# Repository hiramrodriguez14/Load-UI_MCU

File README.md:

# Horizontal Axis Wind Turbine Electronic Control Unit (ECU)

## Load Control & User Interface PCB

Printed Circuit Board (PCB) design for the **Load Control & User Interface (Load & UI) MCU** of the **Horizontal Axis Wind Turbine Electronic Control Unit (ECU)**.

This repository contains the complete KiCad hardware design, manufacturing files, and production documentation for the embedded controller responsible for battery charging, power management, user interaction, and system monitoring.

---

# Documentation & Demo

| Resource | Link |
| ------------------------ | ------------------------------- |
| 🎥 Project Demonstration | https://www.youtube.com/watch?v=vS5Ok38P1Jk |
| 📄 Final Project Report | https://drive.google.com/file/d/1cckKhvj7mvzCEbm3IqWp0KvrUp9g6mgg/view?usp=sharing |
| 📚 Technical Appendix | https://drive.google.com/file/d/1xu7MtcffDlpna8_BUkwEc_BfjpQJpUep/view?usp=sharing |

---

# Overview

The Load Control & User Interface PCB serves as the primary electrical control board of the Horizontal Axis Wind Turbine Electronic Control Unit (ECU).

Designed using **KiCad**, this board integrates sensing, power management, user interaction, communication, and data logging into a single embedded platform. It operates alongside the Turbine MCU PCB to provide complete supervision of the wind turbine system.

The PCB was designed with debugging, manufacturability, and future expansion in mind, incorporating dedicated test points, modular circuitry, and production-ready manufacturing files.

---

# Engineering Highlights

- Custom 2-layer PCB
- Designed in KiCad
- Texas Instruments MSPM0G3519
- Dual INA229 Power Monitors
- SEPIC Converter Control
- Battery Management System (BMS)
- LCD User Interface
- Push Button Interface
- Status LEDs
- UART Communication
- microSD Card Interface
- Relay Driver
- Barrel Jack Power Input
- Production-ready Gerber files
- Pick-and-Place (CPL) files
- Manufacturing BOM

---

# Hardware Features

The PCB integrates the following subsystems:

### Power Management

- Battery charging controller
- SEPIC converter interface
- Power monitoring
- Relay control
- Load protection

### User Interface

- 20×4 LCD connector
- Navigation buttons
- Record button
- Start / Stop controls
- Status LEDs

### Communication

- UART interface to Turbine MCU
- Programming interface
- Debug connectors

### Data Logging

- microSD card socket
- Real-Time Clock (RTC)

---

# Hardware Architecture

The Load Control & UI PCB serves as the electrical management hub of the complete ECU.

Primary functions include:

- Battery charging
- Converter control
- Power measurement
- User interaction
- Data logging
- Load protection
- Communication with the Turbine MCU

<p align="center">
<b>Figure 1.</b> Load & UI MCU Architecture
</p>

---

# PCB Design

The board was designed using KiCad following standard PCB design practices for embedded systems.

Design considerations include:

- Component placement optimization
- Short signal routing
- Power integrity
- Ground plane utilization
- Test point accessibility
- Manufacturing compatibility

## Top Layer

<p align="center">
<b>Figure 2.</b> Top Layer PCB Layout
</p>

---

## Bottom Layer

<p align="center">
<b>Figure 3.</b> Bottom Layer PCB Layout
</p>

---

## Combined Layer View

<p align="center">
<b>Figure 4.</b> Combined PCB Layers
</p>

---

## 3D PCB View

<p align="center">
<b>Figure 5.</b> 3D PCB Rendering
</p>

---

# Manufacturing Files

This repository includes all files required for PCB fabrication and assembly.

Included manufacturing assets:

- Gerber files
- Drill files
- Pick-and-Place (CPL)
- Bill of Materials (BOM)
- Complete schematic
- PCB layout

---

# Development Tools

## PCB Design

- KiCad

## Target MCU

- Texas Instruments MSPM0G3519

---

# Repository Structure

```text
HAWT-LoadUI-PCB
│
├── gerbers/                    Manufacturing Gerber files
├── images/                     Documentation images
├── mylib/                      Custom KiCad component library
├── Load-UI_MCU.kicad_pcb       PCB layout
├── Load-UI_MCU.kicad_sch       Main schematic
├── Load-UI_MCU.kicad_pro       KiCad project
├── Load-UI_MCU-final.csv       Manufacturing BOM
├── Load-UI_MCU-all-pos.csv     Pick-and-Place (CPL)
├── load.kicad_sch              Power subsystem schematic
├── ui.kicad_sch                User Interface schematic
├── README.md                   Repository documentation
└── LICENSE                     Project license
```

---

# Related Repositories

| Repository | Description |
| ------------------------ | ----------------------------------------------- |
| HAWT-TurbineMCU-Firmware | Turbine control firmware |
| HAWT-Load_Control_and_UI | Load Control & UI firmware |
| Turbine_MCU              | Turbine MCU PCB |

---

# Authors

- Hiram R. Rodríguez Hernández
- José M. Burgos Guntín
- Sergio A. Meléndez Padilla
- Sergio A. Da Silva López

Department of Electrical & Computer Engineering

University of Puerto Rico – Mayagüez

---

# License

This project was developed for educational and research purposes as part of the Embedded Systems Design course at the University of Puerto Rico – Mayagüez.

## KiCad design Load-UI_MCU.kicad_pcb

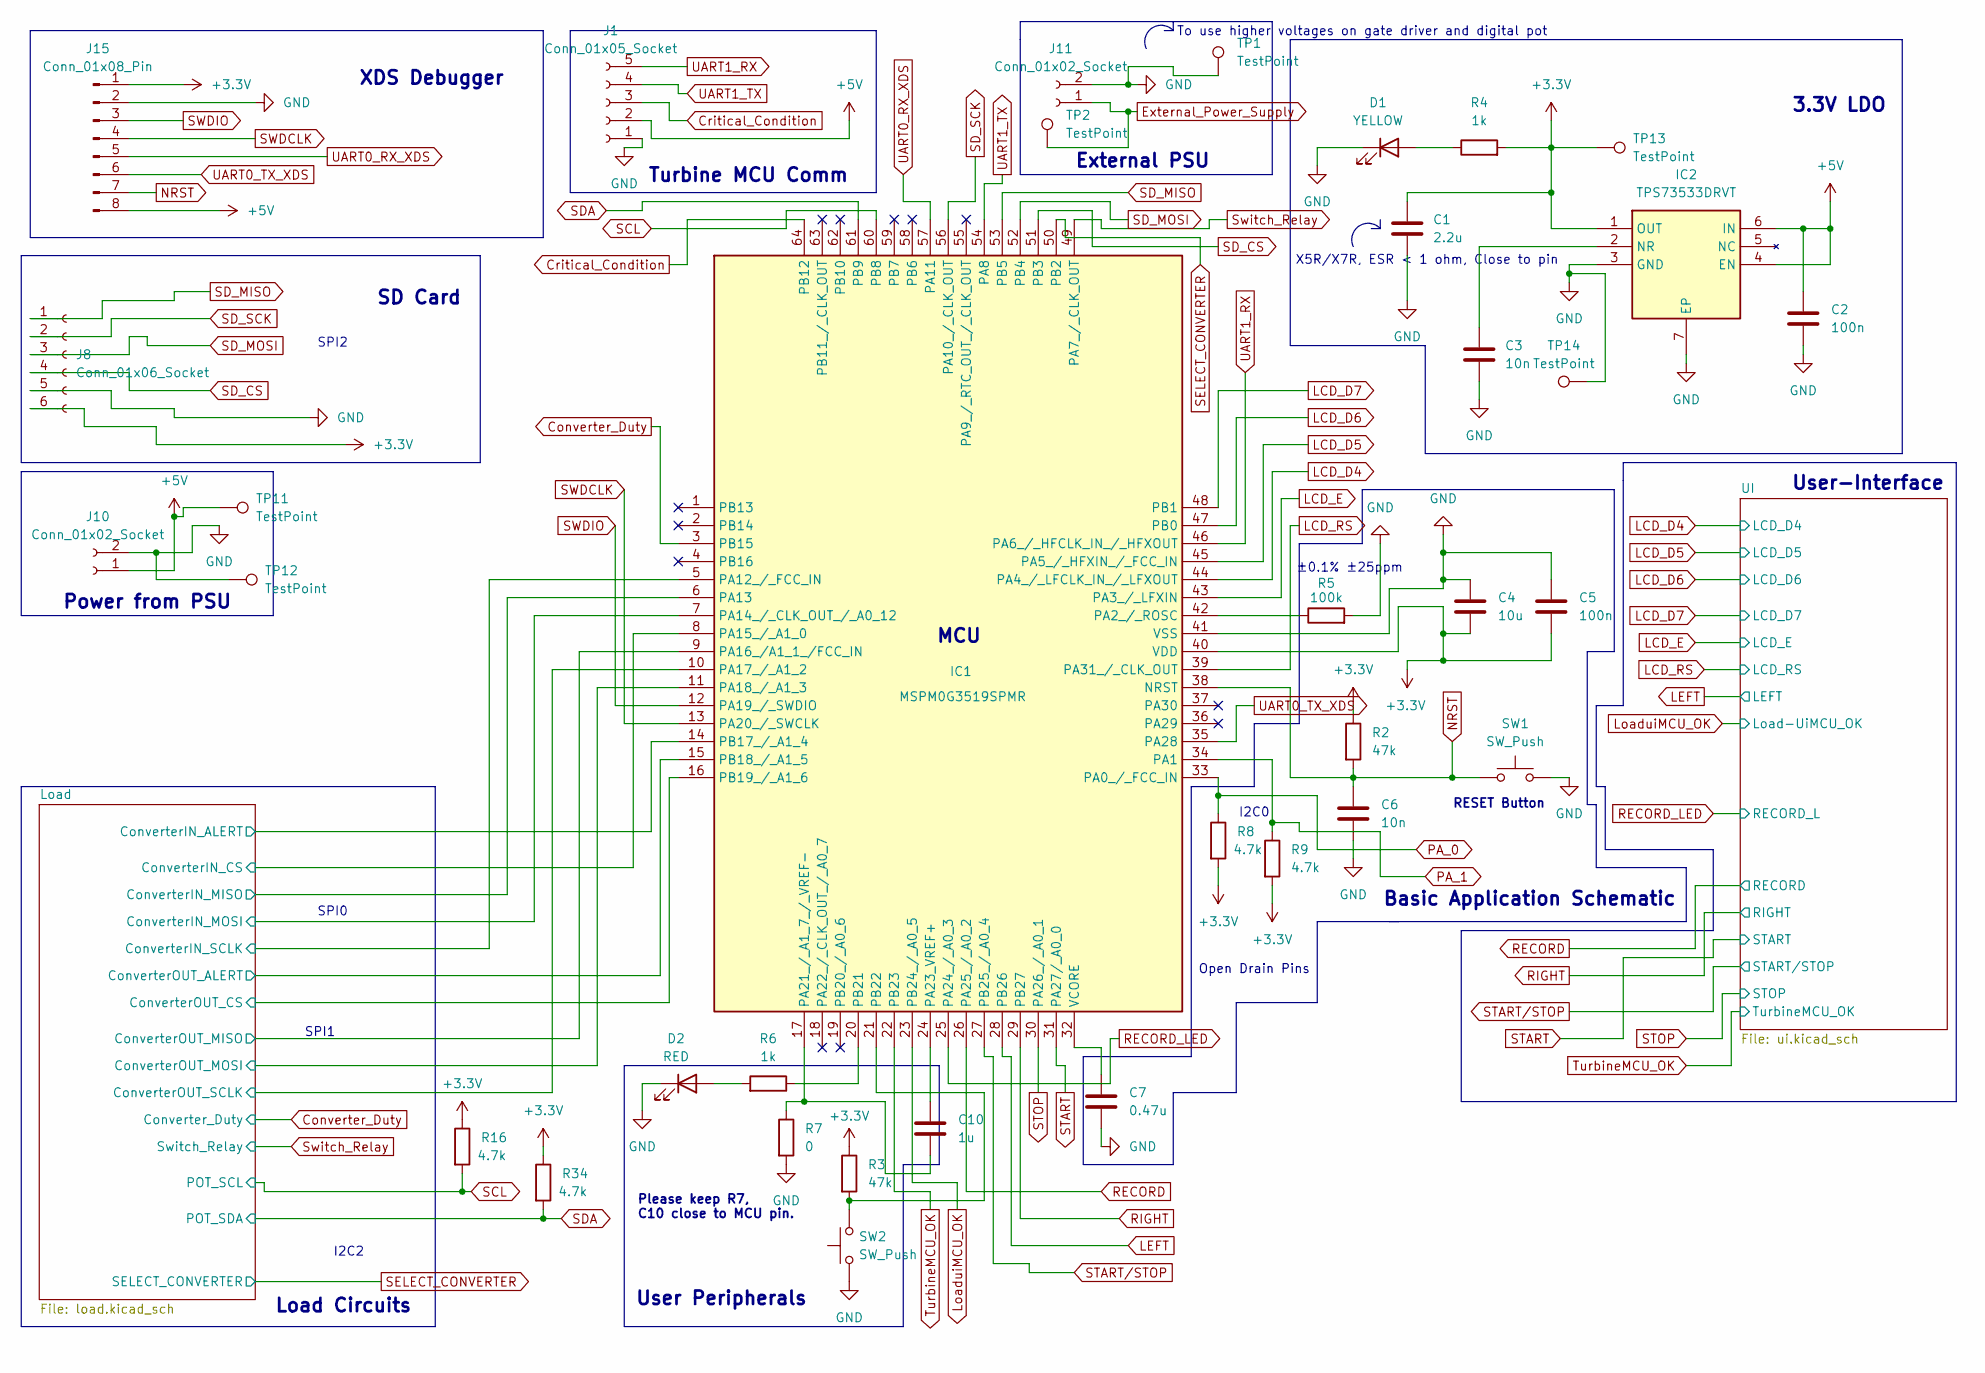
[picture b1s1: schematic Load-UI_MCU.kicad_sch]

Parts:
C1: 2.2u; C_1206_3216Metric_Pad1.33x1.80mm_HandSolder
C2, C5: 100n; C_0805_2012Metric_Pad1.18x1.45mm_HandSolder
C3: 10n; C_0402_1005Metric_Pad0.74x0.62mm_HandSolder
C4: 10u; C_1206_3216Metric_Pad1.33x1.80mm_HandSolder
C6: 10n; C_1206_3216Metric_Pad1.33x1.80mm_HandSolder
C7: 0.47u; C_0805_2012Metric_Pad1.18x1.45mm_HandSolder
C10: 1u; C_0402_1005Metric_Pad0.74x0.62mm_HandSolder
D1: YELLOW; LED_0805_2012Metric_Pad1.15x1.40mm_HandSolder
D2: RED; LED_0603_1608Metric_Pad1.05x0.95mm_HandSolder
IC1: MSPM0G3519SPMR; QFP50P1200X1200X160-64N; Mouser Part Number 595-MSPM0G3507SPMR
IC2: TPS73533DRVT; SON65P200X200X80-7N; Mouser Part Number 595-TPS73533DRVT
J1: Conn_01x05_Socket; JST_XH_B5B-XH-A_1x05_P2.50mm_Vertical
J8: Conn_01x06_Socket; JST_XH_B6B-XH-A_1x06_P2.50mm_Vertical
J10, J11: Conn_01x02_Socket; TerminalBlock_Xinya_XY308-2.54-2P_1x02_P2.54mm_Horizontal
J15: Conn_01x08_Pin; PinHeader_1x08_P2.54mm_Vertical
R2, R3: 47k; R_0805_2012Metric_Pad1.20x1.40mm_HandSolder
R4: 1k; R_0805_2012Metric_Pad1.20x1.40mm_HandSolder
R5: 100k; R_0603_1608Metric_Pad0.98x0.95mm_HandSolder
R6: 1k; R_1206_3216Metric_Pad1.30x1.75mm_HandSolder
R7: 0; R_0402_1005Metric_Pad0.72x0.64mm_HandSolder
R8, R9, R16, R34: 4.7k; R_0805_2012Metric_Pad1.20x1.40mm_HandSolder
SW1, SW2: SW_Push; SW_PUSH_6mm
TP1, TP2, TP11, TP12, TP13, TP14: TestPoint; TestPoint_Pad_D1.0mm

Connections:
+3.3V: C1.1, C4.2, C5.2, IC1.40 (VDD), IC2.1 (OUT), J8.6, J15.1, R2.1, R3.1, R4.2, R8.2, R9.2, R16.1, R34.1, TP13.1; also elsewhere on the board
+5V: C2.1, IC2.4 (EN), IC2.6 (IN), J1.2, J10.1, J15.8, TP11.1; also elsewhere on the board
/Load/ConverterIN_ALERT: IC1.14 (PB17_/_A1_4); also elsewhere on the board
/Load/ConverterIN_CS: IC1.8 (PA15_/_A1_0); also elsewhere on the board
/Load/ConverterIN_MISO: IC1.6 (PA13); also elsewhere on the board
/Load/ConverterIN_MOSI: IC1.7 (PA14_/_CLK_OUT_/_A0_12); also elsewhere on the board
/Load/ConverterIN_SCLK: IC1.5 (PA12_/_FCC_IN); also elsewhere on the board
/Load/ConverterOUT_ALERT: IC1.15 (PB18_/_A1_5); also elsewhere on the board
/Load/ConverterOUT_CS: IC1.16 (PB19_/_A1_6); also elsewhere on the board
/Load/ConverterOUT_MISO: IC1.9 (PA16_/A1_1_/FCC_IN); also elsewhere on the board
/Load/ConverterOUT_MOSI: IC1.11 (PA18_/_A1_3); also elsewhere on the board
/Load/ConverterOUT_SCLK: IC1.10 (PA17_/_A1_2); also elsewhere on the board
Converter_Duty: IC1.3 (PB15); also elsewhere on the board
Critical_Condition: IC1.64 (PB12), J1.3
External_Power_Supply: J11.1, TP2.1; also elsewhere on the board
GND: C1.2, C2.2, C3.2, C4.1, C5.1, C6.2, C7.2, D1.1 (K), D2.1 (K), IC1.41 (VSS), IC2.3 (GND), IC2.7 (EP), J1.1, J8.5, J10.2, J11.2, J15.2, R5.2, R7.2, SW1.2, SW2.1, TP1.1, TP12.1, TP14.1; also elsewhere on the board
LCD_D4: IC1.44 (PA4_/_LFCLK_IN_/_LFXOUT); also elsewhere on the board
LCD_D5: IC1.45 (PA5_/_HFXIN_/_FCC_IN); also elsewhere on the board
LCD_D6: IC1.47 (PB0); also elsewhere on the board
LCD_D7: IC1.48 (PB1); also elsewhere on the board
LCD_E: IC1.43 (PA3_/_LFXIN); also elsewhere on the board
LCD_RS: IC1.39 (PA31_/_CLK_OUT); also elsewhere on the board
LEFT: IC1.28 (PB26); also elsewhere on the board
LoaduiMCU_OK: IC1.23 (PB24_/_A0_5); also elsewhere on the board
NRST: C6.1, IC1.38 (NRST), J15.7, R2.2, SW1.1; also elsewhere on the board
unnamed: D1.2 (A), R4.1
unnamed: D2.2 (A), R6.2
unnamed: IC1.42 (PA2_/_ROSC), R5.1
unnamed: C10.2, IC1.17 (PA21_/_A1_7_/_VREF-), R7.1
unnamed: C10.1, IC1.24 (PA23_VREF+)
unnamed: IC1.20 (PB21), R6.1
unnamed: IC1.21 (PB22), R3.2, SW2.2
unnamed: C7.1, IC1.32 (VCORE)
unnamed: C3.1, IC2.2 (NR)
PA_0: IC1.33 (PA0_/_FCC_IN), R8.1
PA_1: IC1.34 (PA1), R9.1
POT_CS: IC1.1 (PB13)
RECORD: IC1.26 (PA25_/_A0_2); also elsewhere on the board
RECORD_LED: IC1.25 (PA24_/_A0_3); also elsewhere on the board
RIGHT: IC1.29 (PB27); also elsewhere on the board
SCL: IC1.60 (PB8), R16.2; also elsewhere on the board
SDA: IC1.61 (PB9), R34.2; also elsewhere on the board
SD_CS: IC1.51 (PB3), J8.4
SD_MISO: IC1.53 (PB5), J8.1
SD_MOSI: IC1.52 (PB4), J8.3
SD_SCK: IC1.56 (PA10_/_CLK_OUT), J8.2
SELECT_CONVERTER: IC1.50 (PB2); also elsewhere on the board
START: IC1.31 (PA27/_A0_0); also elsewhere on the board
START/STOP: IC1.27 (PB25_/_A0_4); also elsewhere on the board
STOP: IC1.30 (PA26_/_A0_1); also elsewhere on the board
SWDCLK: IC1.13 (PA20_/_SWCLK), J15.4
SWDIO: IC1.12 (PA19_/_SWDIO), J15.3
Switch_Relay: IC1.49 (PA7_/_CLK_OUT); also elsewhere on the board
TurbineMCU_OK: IC1.22 (PB23); also elsewhere on the board
UART0_RX_XDS: IC1.57 (PA11), J15.5
UART0_TX_XDS: IC1.35 (PA28), J15.6
UART1_RX: IC1.46 (PA6_/_HFCLK_IN_/_HFXOUT), J1.5
UART1_TX: IC1.54 (PA8), J1.4

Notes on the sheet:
To use higher voltages on gate driver and digital pot
SPI1
User Peripherals
MCU
SPI2
Basic Application Schematic
Load Circuits
RESET Button
User-Interface
Power from PSU
±0.1% ±25ppm
I2C0
SPI0
SD Card
External PSU
XDS Debugger
Please keep R7, C10 close to MCU pin.
3.3V LDO
I2C2
Open Drain Pins
X5R/X7R, ESR < 1 ohm, Close to pin
Turbine MCU Comm

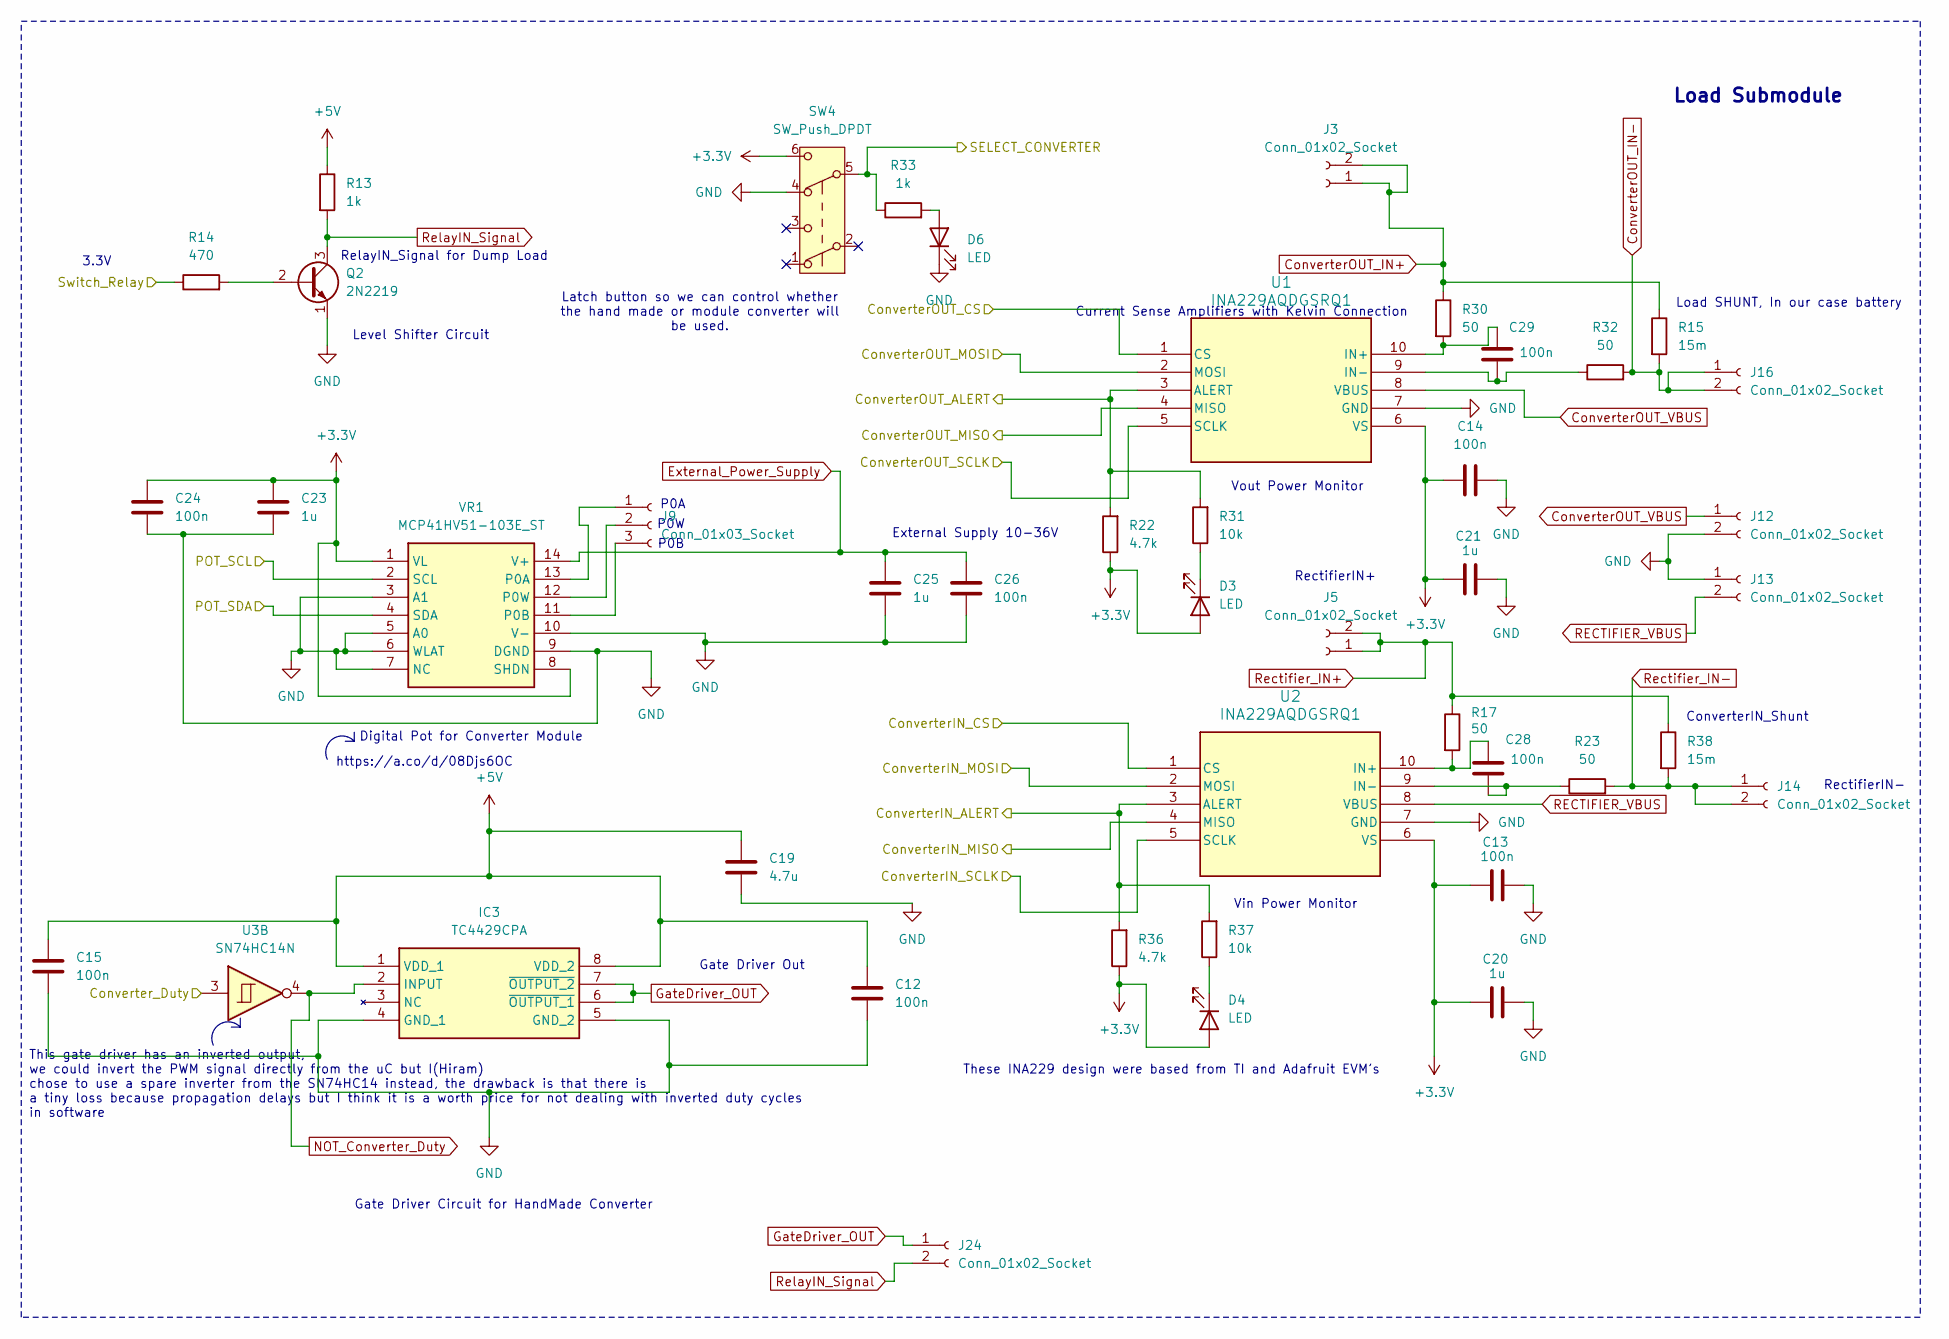
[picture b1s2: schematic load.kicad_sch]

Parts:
C12, C13, C14, C15, C24, C26: 100n; C_0805_2012Metric_Pad1.18x1.45mm_HandSolder
C19: 4.7u; C_1206_3216Metric_Pad1.33x1.80mm_HandSolder
C20, C21, C23, C25: 1u; C_1206_3216Metric_Pad1.33x1.80mm_HandSolder
C28, C29: 100n; C_0402_1005Metric_Pad0.74x0.62mm_HandSolder
D3, D4, D6: LED; LED_0805_2012Metric_Pad1.15x1.40mm_HandSolder
IC3: TC4429CPA; CERDIP-8_W7.62mm_SideBrazed; Mouser Part Number 579-TC4429CPA
J3, J5, J12, J13, J14, J16, J24: Conn_01x02_Socket; TerminalBlock_Xinya_XY308-2.54-2P_1x02_P2.54mm_Horizontal
J9: Conn_01x03_Socket; JST_XH_B3B-XH-A_1x03_P2.50mm_Vertical
Q2: 2N2219; TO-92_Inline
R13: 1k; R_0805_2012Metric_Pad1.20x1.40mm_HandSolder
R14: 470; R_0805_2012Metric_Pad1.20x1.40mm_HandSolder
R15, R38: 15m; R_1206_3216Metric_Pad1.30x1.75mm_HandSolder
R17, R23, R30, R32: 50; R_0402_1005Metric_Pad0.72x0.64mm_HandSolder
R22, R36: 4.7k; R_1206_3216Metric_Pad1.30x1.75mm_HandSolder
R31, R37: 10k; R_1206_3216Metric_Pad1.30x1.75mm_HandSolder
R33: 1k; R_1206_3216Metric_Pad1.30x1.75mm_HandSolder
SW4: SW_Push_DPDT; SW_DPDT_XLX
U1, U2: INA229AQDGSRQ1; VSSOP-10_3x3mm_P0.5mm
U3: SN74HC14N; CERDIP-14_W7.62mm_SideBrazed
VR1: MCP41HV51-103E_ST; TSSOP-14_4.4x5mm_P0.65mm; Mouser Part Number 579-MCP41HV51-103EST

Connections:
+3.3V: C13.1, C14.1, C20.1, C21.1, C23.1, C24.1, D3.2 (A), D4.2 (A), R22.1, R36.1, SW4.6 (C), U1.6 (VS), U2.6 (VS), VR1.1 (VL), VR1.8 (SHDN); also elsewhere on the board
+5V: C12.1, C15.1, C19.1, IC3.1 (VDD_1), IC3.8 (VDD_2), R13.1; also elsewhere on the board
/Load/ConverterIN_ALERT: R36.2, R37.2, U2.3 (ALERT); also elsewhere on the board
/Load/ConverterIN_CS: U2.1 (CS); also elsewhere on the board
/Load/ConverterIN_MISO: U2.4 (MISO); also elsewhere on the board
/Load/ConverterIN_MOSI: U2.2 (MOSI); also elsewhere on the board
/Load/ConverterIN_SCLK: U2.5 (SCLK); also elsewhere on the board
/Load/ConverterOUT_ALERT: R22.2, R31.2, U1.3 (ALERT); also elsewhere on the board
/Load/ConverterOUT_CS: U1.1 (CS); also elsewhere on the board
/Load/ConverterOUT_MISO: U1.4 (MISO); also elsewhere on the board
/Load/ConverterOUT_MOSI: U1.2 (MOSI); also elsewhere on the board
/Load/ConverterOUT_SCLK: U1.5 (SCLK); also elsewhere on the board
ConverterOUT_IN+: J3.1, J3.2, R15.1, R30.1
ConverterOUT_IN-: J16.1, J16.2, R15.2, R32.2
ConverterOUT_VBUS: J12.1, U1.8 (VBUS)
Converter_Duty: U3.3; also elsewhere on the board
External_Power_Supply: C25.1, C26.1, VR1.14 (V+); also elsewhere on the board
GND: C12.2, C13.2, C14.2, C15.2, C19.2, C20.2, C21.2, C23.2, C24.2, C25.2, C26.2, D6.1 (K), IC3.4 (GND_1), IC3.5 (GND_2), J12.2, J13.1, Q2.1 (E), SW4.4 (A), U1.7 (GND), U2.7 (GND), VR1.3 (A1), VR1.5 (A0), VR1.6 (WLAT), VR1.7 (NC), VR1.9 (DGND), VR1.10 (V-); also elsewhere on the board
GateDriver_OUT: IC3.6 (~OUTPUT_1), IC3.7 (~OUTPUT_2), J24.1
NOT_Converter_Duty: IC3.2 (INPUT), U3.4
unnamed: D3.1 (K), R31.1
unnamed: D4.1 (K), R37.1
unnamed: D6.2 (A), R33.2
unnamed: J9.1, VR1.13 (P0A)
unnamed: J9.2, VR1.12 (P0W)
unnamed: J9.3, VR1.11 (P0B)
unnamed: Q2.2 (B), R14.2
unnamed: C29.1, R30.2, U1.10 (IN+)
unnamed: C29.2, R32.1, U1.9 (IN-)
unnamed: C28.1, R17.2, U2.10 (IN+)
unnamed: C28.2, R23.1, U2.9 (IN-)
RECTIFIER_VBUS: J13.2, U2.8 (VBUS)
Rectifier_IN+: J5.1, J5.2, R17.1, R38.1
Rectifier_IN-: J14.1, J14.2, R23.2, R38.2
RelayIN_Signal: J24.2, Q2.3 (C), R13.2
SCL: VR1.2 (SCL); also elsewhere on the board
SDA: VR1.4 (SDA); also elsewhere on the board
SELECT_CONVERTER: R33.1, SW4.5 (B); also elsewhere on the board
Switch_Relay: R14.1; also elsewhere on the board

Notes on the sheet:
Latch button so we can control whether the hand made or module converter will be used.
Load SHUNT, In our case battery
3.3V
Vin Power Monitor
RectifierIN-
Current Sense Amplifiers with Kelvin Connection
External Supply 10-36V
Load Submodule
Level Shifter Circuit
RectifierIN+
These INA229 design were based from TI and Adafruit EVM's
P0A
P0W
Vout Power Monitor
RelayIN_Signal for Dump Load
Digital Pot for Converter Module
This gate driver has an inverted output, we could invert the PWM signal directly from the uC but I(Hiram) chose to use a spare inverter from the SN74HC14 instead, the drawback is that there is a tiny loss because propagation delays but I think it is a worth price for not dealing with inverted duty 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
ConverterIN_Shunt
Gate Driver Circuit for HandMade Converter
https://a.co/d/08Djs6OC
Gate Driver Out
P0B

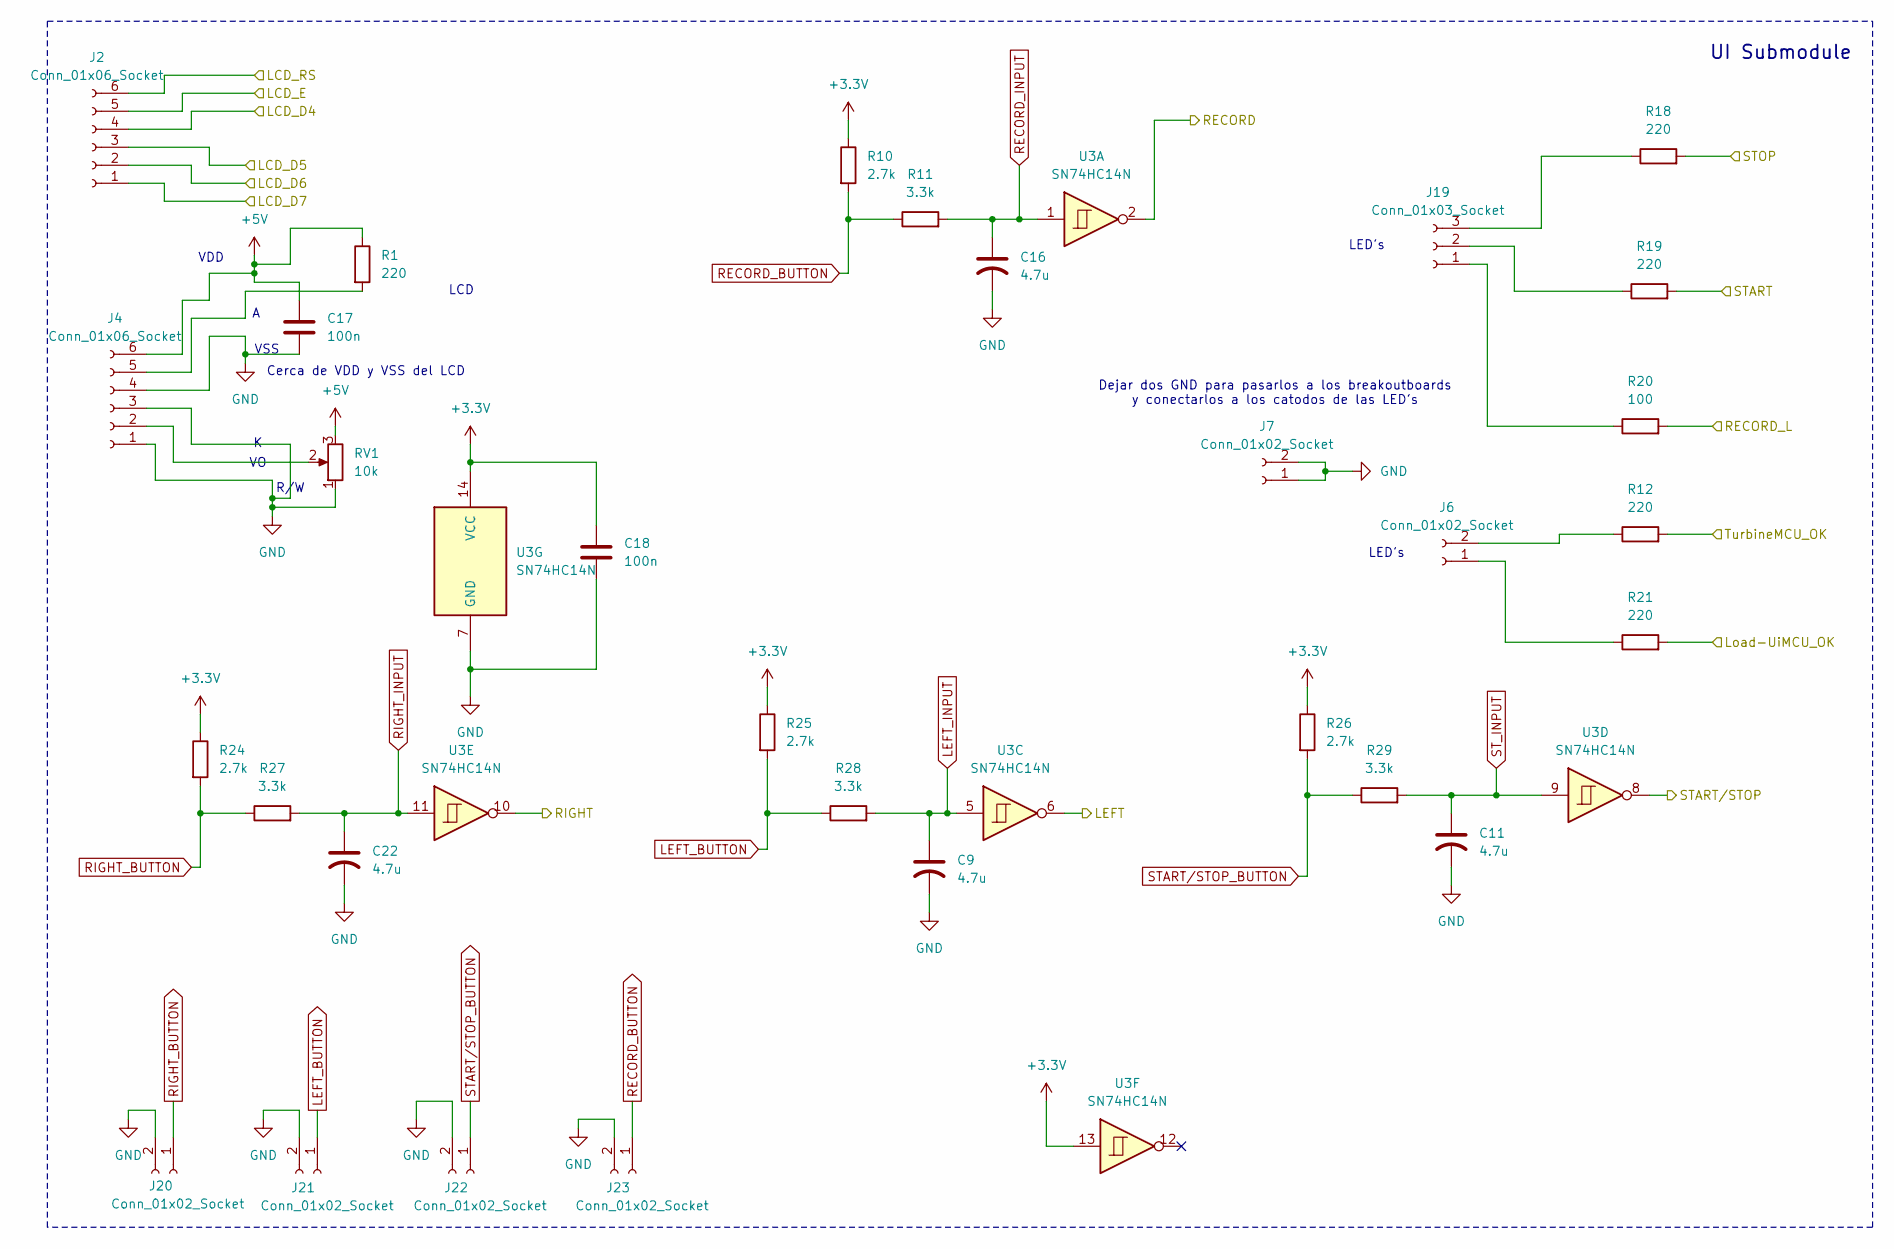
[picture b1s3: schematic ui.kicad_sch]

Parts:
C9, C11, C16, C22: 4.7u; C_1206_3216Metric_Pad1.33x1.80mm_HandSolder
C17, C18: 100n; C_0805_2012Metric_Pad1.18x1.45mm_HandSolder
J2, J4: Conn_01x06_Socket; JST_XH_B6B-XH-A_1x06_P2.50mm_Vertical
J6, J20, J21, J22, J23: Conn_01x02_Socket; JST_XH_B2B-XH-A_1x02_P2.50mm_Vertical
J7: Conn_01x02_Socket; TerminalBlock_Xinya_XY308-2.54-2P_1x02_P2.54mm_Horizontal
J19: Conn_01x03_Socket; JST_XH_B3B-XH-A_1x03_P2.50mm_Vertical
R1, R12, R18, R19, R21: 220; R_Axial_DIN0207_L6.3mm_D2.5mm_P7.62mm_Horizontal
R10, R24, R25, R26: 2.7k; R_0805_2012Metric_Pad1.20x1.40mm_HandSolder
R11, R27, R28, R29: 3.3k; R_0805_2012Metric_Pad1.20x1.40mm_HandSolder
R20: 100; R_Axial_DIN0207_L6.3mm_D2.5mm_P7.62mm_Horizontal
RV1: 10k; Potentiometer_Bourns_3296W_Vertical
U3: SN74HC14N; CERDIP-14_W7.62mm_SideBrazed

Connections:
+3.3V: C18.1, R10.1, R24.1, R25.1, R26.1, U3.13, U3.14 (VCC); also elsewhere on the board
+5V: C17.1, J4.6, R1.1, RV1.3; also elsewhere on the board
GND: C9.2, C11.2, C16.2, C17.2, C18.2, C22.2, J4.1, J4.3, J4.4, J7.1, J7.2, J20.2, J21.2, J22.2, J23.2, RV1.1, U3.7 (GND); also elsewhere on the board
LCD_D4: J2.4; also elsewhere on the board
LCD_D5: J2.3; also elsewhere on the board
LCD_D6: J2.2; also elsewhere on the board
LCD_D7: J2.1; also elsewhere on the board
LCD_E: J2.5; also elsewhere on the board
LCD_RS: J2.6; also elsewhere on the board
LEFT: U3.6; also elsewhere on the board
LEFT_BUTTON: J21.1, R25.2, R28.1
LEFT_INPUT: C9.1, R28.2, U3.5
LoaduiMCU_OK: R21.2; also elsewhere on the board
unnamed: J4.2, RV1.2
unnamed: J4.5, R1.2
unnamed: J6.1, R21.1
unnamed: J6.2, R12.1
unnamed: J19.1, R20.1
unnamed: J19.2, R19.1
unnamed: J19.3, R18.1
RECORD: U3.2; also elsewhere on the board
RECORD_BUTTON: J23.1, R10.2, R11.1
RECORD_INPUT: C16.1, R11.2, U3.1
RECORD_LED: R20.2; also elsewhere on the board
RIGHT: U3.10; also elsewhere on the board
RIGHT_BUTTON: J20.1, R24.2, R27.1
RIGHT_INPUT: C22.1, R27.2, U3.11
START: R19.2; also elsewhere on the board
START/STOP: U3.8; also elsewhere on the board
START/STOP_BUTTON: J22.1, R26.2, R29.1
STOP: R18.2; also elsewhere on the board
ST_INPUT: C11.1, R29.2, U3.9
TurbineMCU_OK: R12.2; also elsewhere on the board

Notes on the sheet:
LCD
VSS
Cerca de VDD y VSS del LCD
Dejar dos GND para pasarlos a los breakoutboards y conectarlos a los catodos de las LED's
LED's
UI Submodule
VDD
R/W

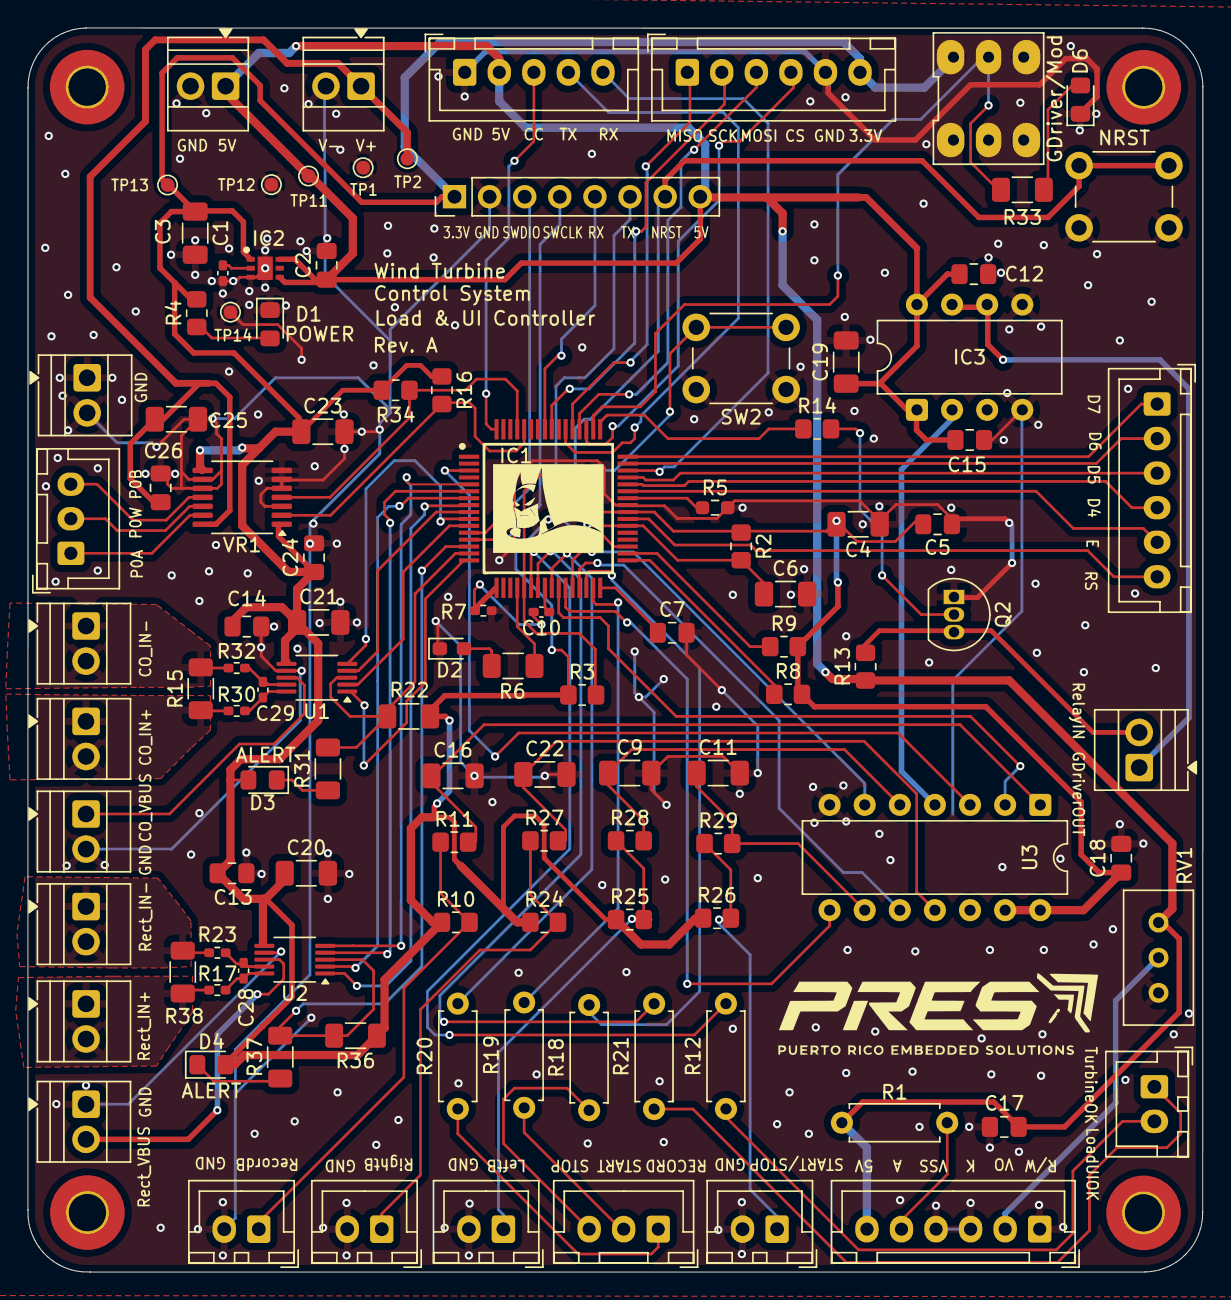
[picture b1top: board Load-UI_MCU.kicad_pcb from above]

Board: 4 copper layers, 85.0 x 90.0 mm, 109 parts (0 on the bottom side), 92 nets.

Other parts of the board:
NRST: SW_Push; SW_PUSH_6mm

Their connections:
GND: NRST.2; also elsewhere on the board
NRST: NRST.1; also elsewhere on the board

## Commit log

2026-04-30 Initial KiCad project commit
2026-04-30 Updated schematic and cleaned autosave files
2026-04-30 Changed NRST button silkscreen
2026-04-30 removed unnecessary vias
2026-05-01 Added final changes to PCB: 1. Fixed OV2 ressitors on Power MUX, 2. Added input filtering on both INA229, 3. Changed the LDO layout based on manufacturer recomendations.
2026-05-01 Finished pcb for manufacturing, changed some footprints based on what the manufacturer had. Also I fixed the potentiometer footprint.
2026-05-01 final BOM
2026-05-04 Removed unnecessary hex inverter, fixed record button connection, change relay resistors to smd
2026-05-05 Added testpoints
2026-05-05 schematic comments
2026-05-17 Last update after PR4, mostly done I need revisions from rest of members with special attention on grounding layout
2026-05-18 added two more testpoints
2026-05-19 PCB finished, only final manufacturing files left, BOM, CPL
2026-05-20 ready for manufacturing
2026-05-21 This commit contains all files up dote to Rev A. Load & UI MCU, manufactured on May 21, 2026
2026-06-21 Update architecture image and caption in README
2026-06-21 Update repository name in README
2026-06-21 Fix typo in Turbine MCU repository name
